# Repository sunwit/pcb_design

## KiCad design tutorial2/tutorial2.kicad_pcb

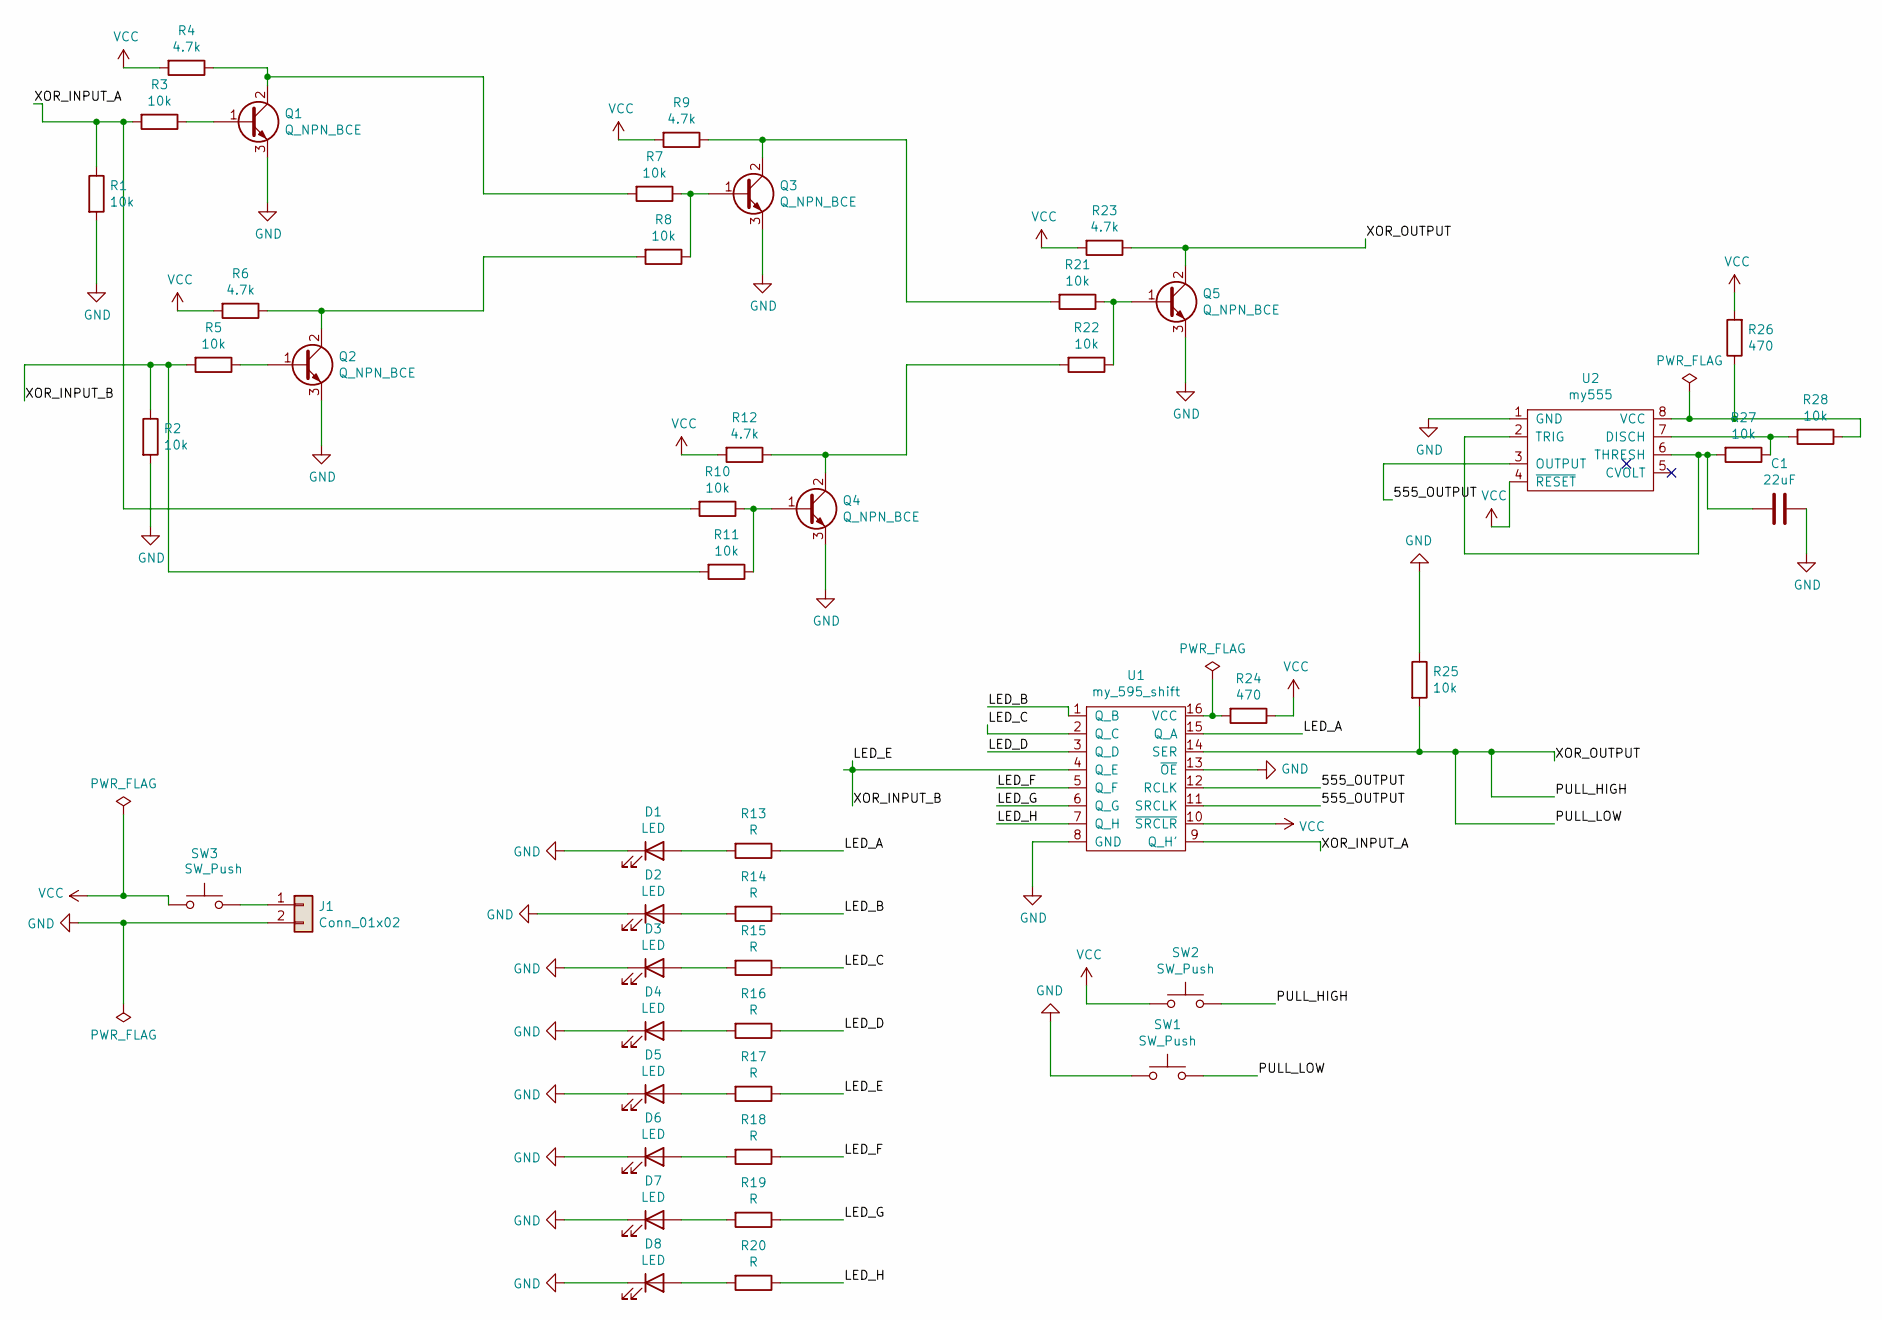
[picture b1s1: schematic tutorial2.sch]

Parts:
C1: 22uF; C_3640_9110Metric_Pad2.10x10.45mm_HandSolder
D1, D2, D3, D4, D5, D6, D7, D8: LED; LED_D3.0mm
J1: Conn_01x02; JWT_A3963_1x02_P3.96mm_Vertical
Q1, Q2, Q3, Q4, Q5: Q_NPN_BCE; SW_SPST_B3U-3100P-B
R1, R2, R3, R5, R7, R8, R10, R11, R21, R22, R25, R27, R28: 10k; R_2816_7142Metric
R4, R6, R9, R12, R23: 4.7k; R_2816_7142Metric
R13, R14, R15, R16, R17, R18, R19, R20: R; R_2816_7142Metric
R24, R26: 470; R_2816_7142Metric
SW1, SW2: SW_Push; myswitch
SW3: SW_Push; SW_Tactile_SPST_Angled_PTS645Vx83-2LFS
U1: my_595_shift; DIP_Socket-16_W4.3_W5.08_W7.62_W10.16_W10.9_3M_216-3340-00-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
U2: my555; 3M_Textool_240-1288-00-0602J_2x20_P2.54mm

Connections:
/555_OUTPUT: U1.11 (SRCLK), U1.12 (RCLK), U2.3 (OUTPUT)
/LED_A: R13.1, U1.15 (Q_A)
/LED_B: R14.1, U1.1 (Q_B)
/LED_C: R15.1, U1.2 (Q_C)
/LED_D: R16.1, U1.3 (Q_D)
/LED_E: R2.1, R5.2, R11.2, R17.1, U1.4 (Q_E)
/LED_F: R18.1, U1.5 (Q_F)
/LED_G: R19.1, U1.6 (Q_G)
/LED_H: R20.1, U1.7 (Q_H)
/PULL_HIGH: Q5.2 (C), R23.1, R25.2, SW1.2, SW2.2, U1.14 (SER)
/XOR_INPUT_A: R1.1, R3.2, R10.2, U1.9 (Q_H')
GND: C1.1, D1.1 (K), D2.1 (K), D3.1 (K), D4.1 (K), D5.1 (K), D6.1 (K), D7.1 (K), D8.1 (K), J1.2, Q1.3 (E), Q2.3 (E), Q3.3 (E), Q4.3 (E), Q5.3 (E), R1.2, R2.2, R25.1, SW1.1, U1.8 (GND), U1.13 (~OE), U2.1 (GND)
unnamed: C1.2, R27.2, U2.2 (TRIG), U2.6 (THRESH)
unnamed: D1.2 (A), R13.2
unnamed: D2.2 (A), R14.2
unnamed: D3.2 (A), R15.2
unnamed: D4.2 (A), R16.2
unnamed: D5.2 (A), R17.2
unnamed: D6.2 (A), R18.2
unnamed: D7.2 (A), R19.2
unnamed: D8.2 (A), R20.2
unnamed: J1.1, SW3.2
unnamed: Q1.1 (B), R3.1
unnamed: Q1.2 (C), R4.1, R7.2
unnamed: Q2.1 (B), R5.1
unnamed: Q2.2 (C), R6.1, R8.2
unnamed: Q3.1 (B), R7.1, R8.1
unnamed: Q3.2 (C), R9.1, R21.2
unnamed: Q4.1 (B), R10.1, R11.1
unnamed: Q4.2 (C), R12.1, R22.2
unnamed: Q5.1 (B), R21.1, R22.1
unnamed: R24.2, U1.16 (VCC)
unnamed: R26.1, R28.1, U2.8 (VCC)
unnamed: R27.1, R28.2, U2.7 (DISCH)
VCC: R4.2, R6.2, R9.2, R12.2, R23.2, R24.1, R26.2, SW2.1, SW3.1, U1.10 (~SRCLR), U2.4 (~RESET)

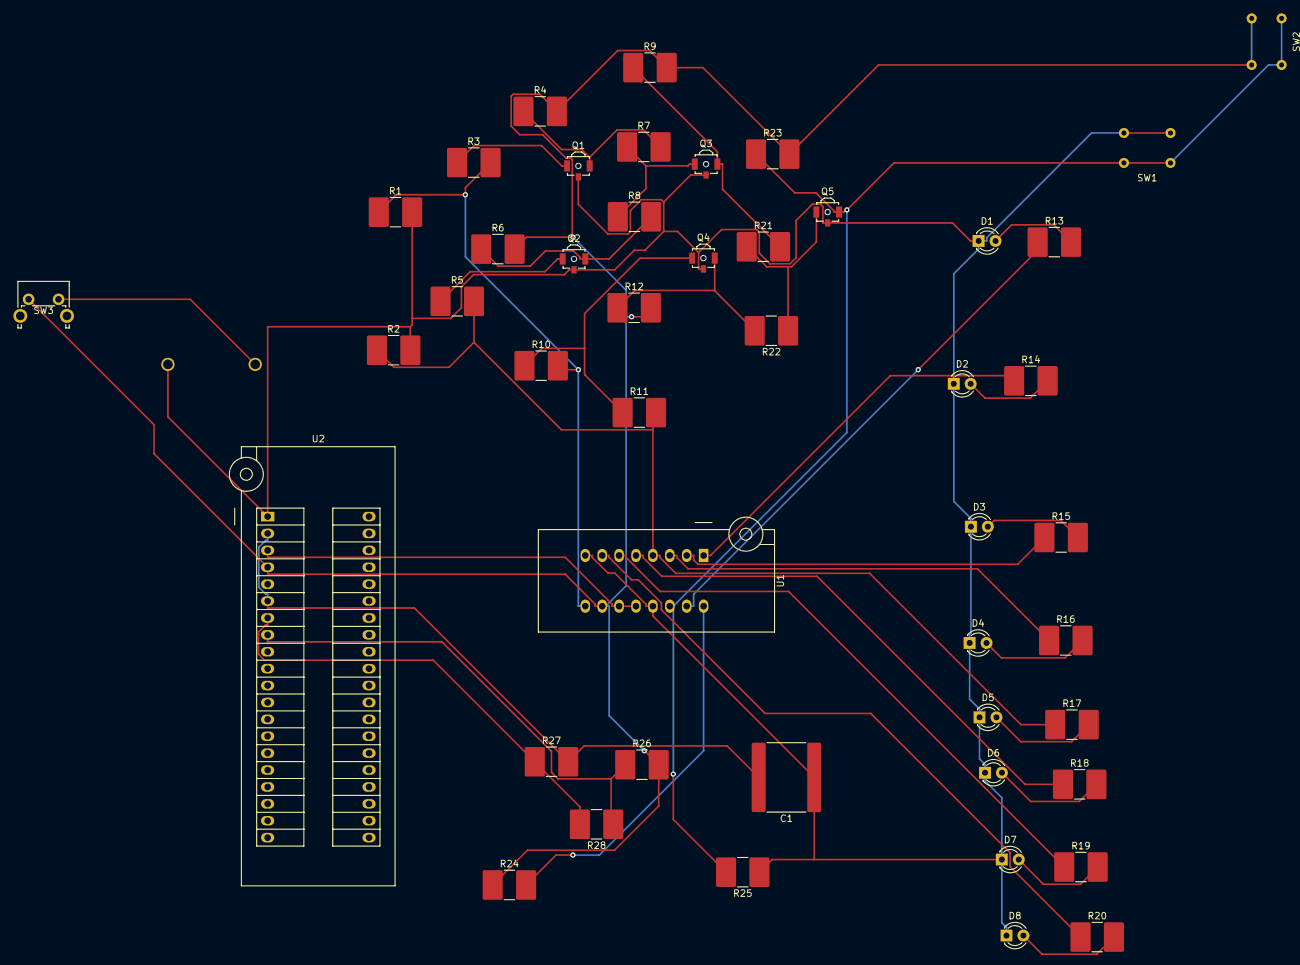
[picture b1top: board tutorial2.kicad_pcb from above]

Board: 2 copper layers, 48 parts (1 on the bottom side), 35 nets.

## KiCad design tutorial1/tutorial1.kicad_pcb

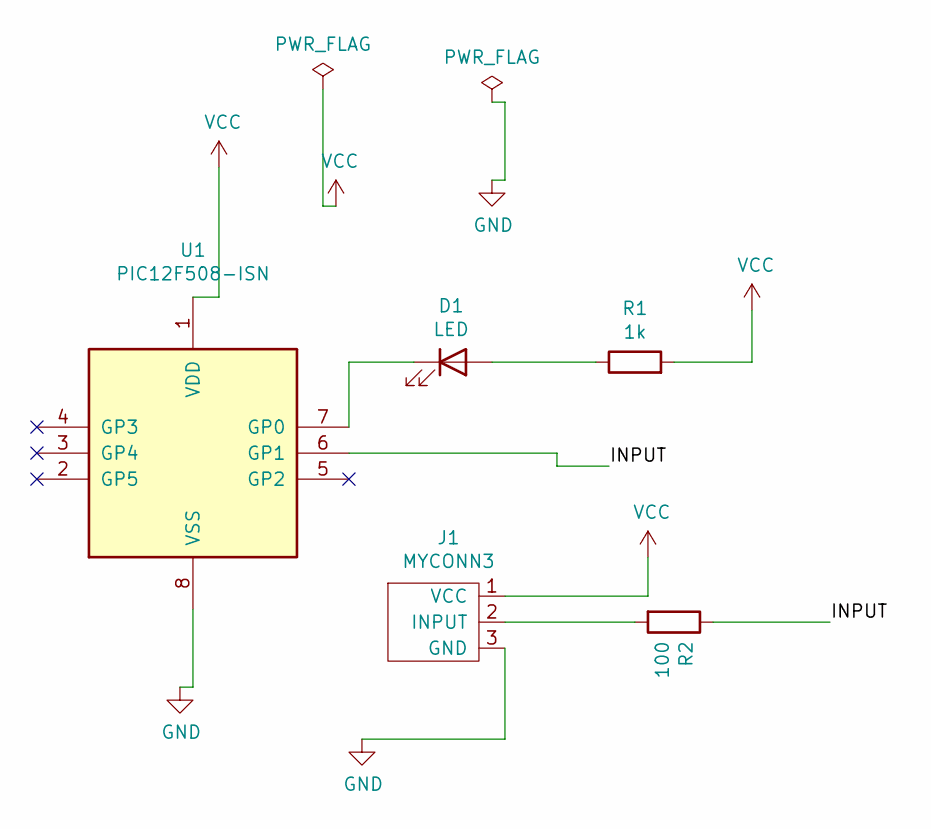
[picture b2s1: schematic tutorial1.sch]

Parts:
D1: LED; LED_D5.0mm
J1: MYCONN3; Banana_Jack_3Pin
R1: 1k; R_Axial_DIN0207_L6.3mm_D2.5mm_P2.54mm_Vertical
R2: 100; R_Axial_DIN0207_L6.3mm_D2.5mm_P2.54mm_Vertical
U1: PIC12F508-ISN; DIP-8_W7.62mm

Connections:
/INPUT: R2.1, U1.6 (GP1)
GND: J1.3 (GND), U1.8 (VSS)
unnamed: D1.1 (K), U1.7 (GP0)
unnamed: D1.2 (A), R1.1
unnamed: J1.2 (INPUT), R2.2
VCC: J1.1 (VCC), R1.2, U1.1 (VDD)

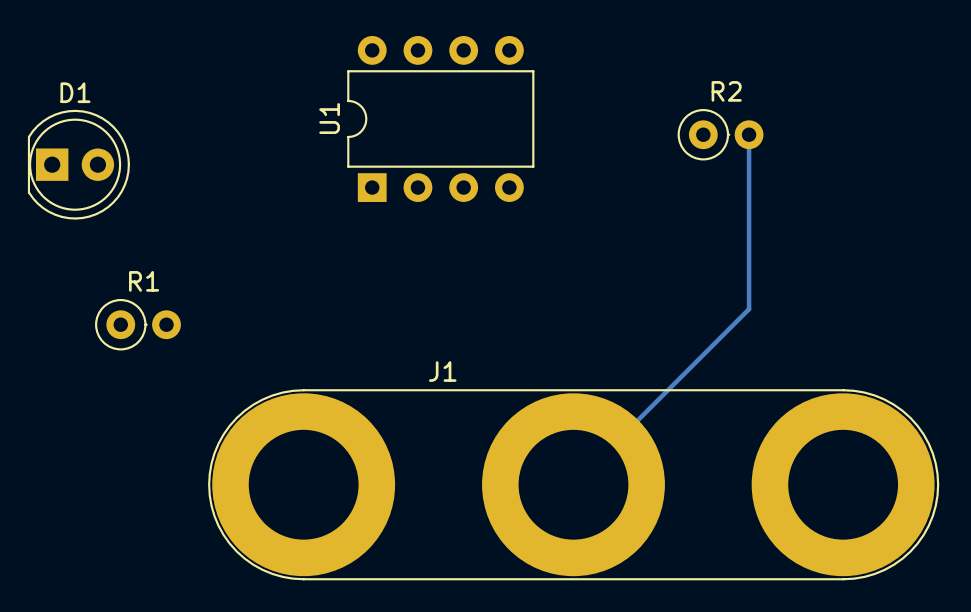
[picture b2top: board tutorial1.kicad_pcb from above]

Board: 4 copper layers, 5 parts (0 on the bottom side), 6 nets.

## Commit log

2020-08-21 first
